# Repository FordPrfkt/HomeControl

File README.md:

# HomeControl
Home automation system build around RFM69

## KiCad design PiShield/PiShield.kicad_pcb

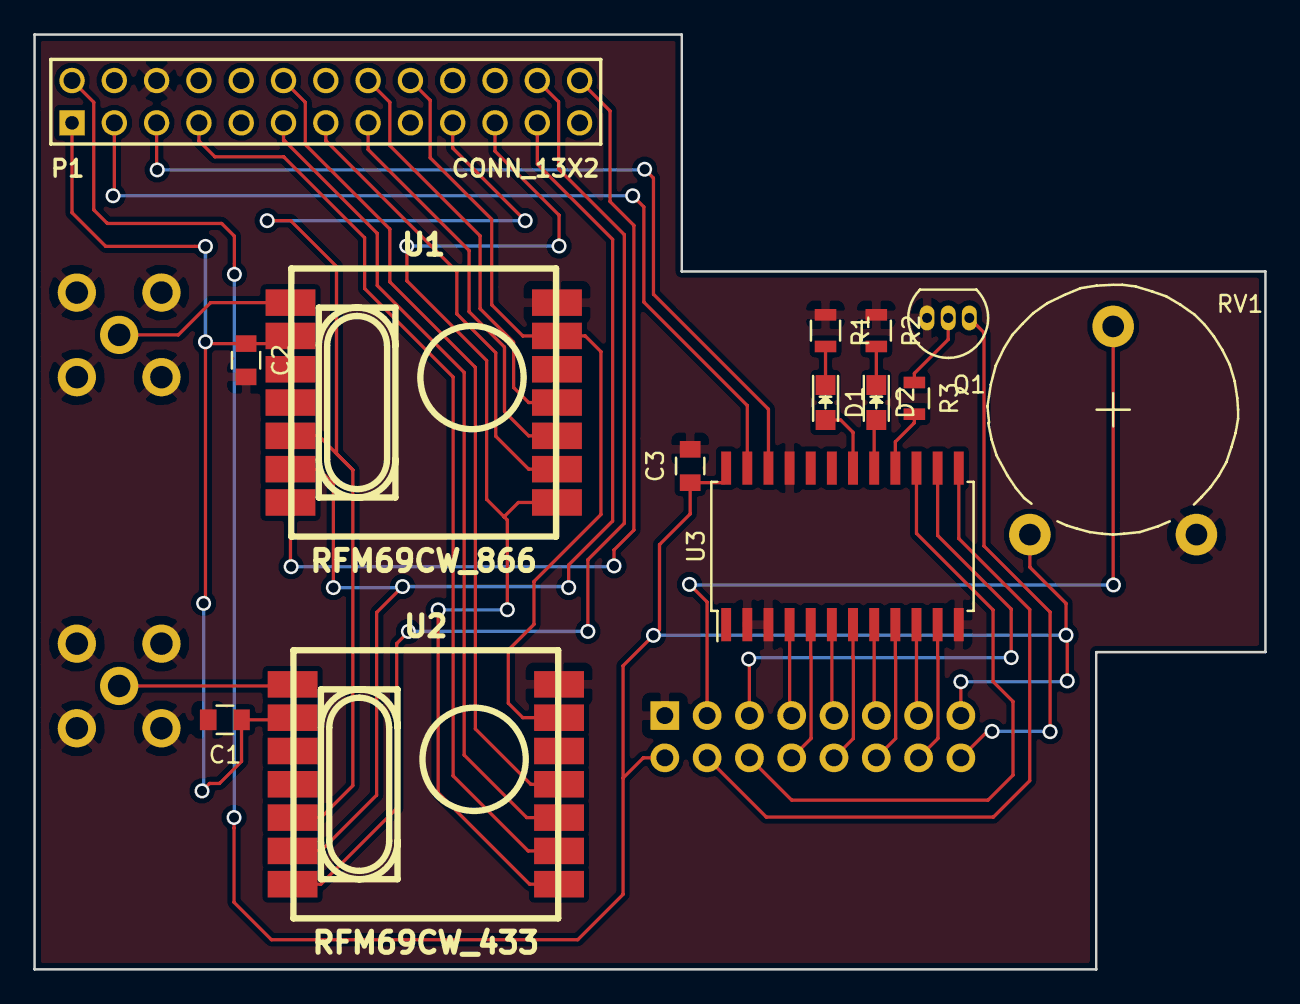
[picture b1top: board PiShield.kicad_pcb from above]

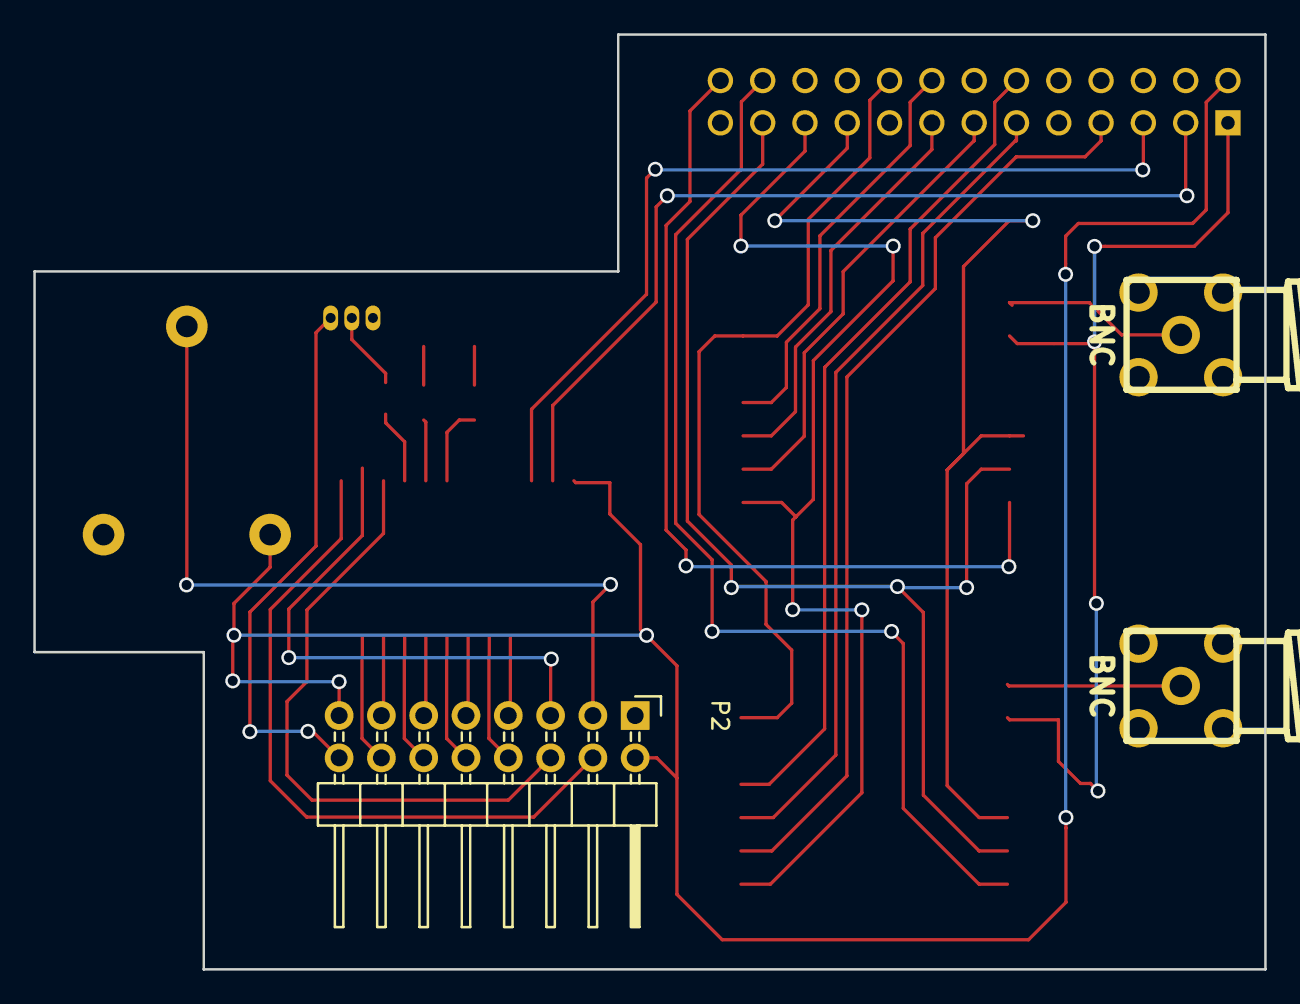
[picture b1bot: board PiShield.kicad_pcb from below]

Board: 2 copper layers, 73.9 x 56.1 mm, 17 parts (3 on the bottom side), 38 nets.

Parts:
C1, C2, C3: 100nF; C_0805
D1, D2: LED; LED_0805
P1: CONN_13X2; pin_array_13x2
P2: CONN_01X16; Pin_Header_Angled_2x08
P3, P4: BNC; sma_90_r300.124.403
Q1: BC547; TO-92_Inline_Narrow_Oval
R1, R2, R3: R; R_0805
RV1: POT; Potentiometer_Trimmer-Piher_PT15-V12-5_horizontal
U1: RFM69CW_866; RFM12B_SMD
U2: RFM69CW_433; RFM12B_SMD
U3: PCA9555; SOIC-24_7.5x15.4mm_Pitch1.27mm

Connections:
+3.3V: C1.1, C2.1, P1.1, U1.2, U2.2
+5V: C3.1, P1.2, P2.2, P2.15, RV1.1, U3.24
CS_433: P1.24, U2.7
CS_866: P1.26, U1.7
DIO0_433: P1.7, U2.9
DIO0_866: P1.13, U1.9
DIO1_433: P1.12, U2.11
DIO1_866: P1.16, U1.11
DIO2_433: P1.11, U2.10
DIO2_866: P1.15, U1.10
GND: C1.2, C2.2, C3.2, P1.6, P2.1, P3.2, P4.2, Q1.3, R1.1, R2.1, RV1.3, U1.14, U2.14, U3.2, U3.3, U3.12, U3.21
MISO: P1.21, U1.8, U2.8
MOSI: P1.19, U1.5, U2.5
unnamed: D1.1, R1.2
unnamed: D1.2, U3.18
unnamed: D2.1, R2.2
unnamed: D2.2, U3.17
unnamed: P2.3, RV1.2
unnamed: P2.4, U3.13
unnamed: P2.5, U3.14
unnamed: P2.6, U3.15
unnamed: P2.7, U3.4
unnamed: P2.8, U3.5
unnamed: P2.9, U3.6
unnamed: P2.10, U3.7
unnamed: P2.11, U3.8
unnamed: P2.12, U3.9
unnamed: P2.13, U3.10
unnamed: P2.14, U3.11
unnamed: P2.16, Q1.1
unnamed: P3.1, U2.1
unnamed: P4.1, U1.1
unnamed: Q1.2, R3.1
unnamed: R3.2, U3.16
Reset_RF: P1.18, U1.13, U2.13
SCK: P1.23, U1.6, U2.6
SCL: P1.5, U3.22
SDA: P1.3, U3.23

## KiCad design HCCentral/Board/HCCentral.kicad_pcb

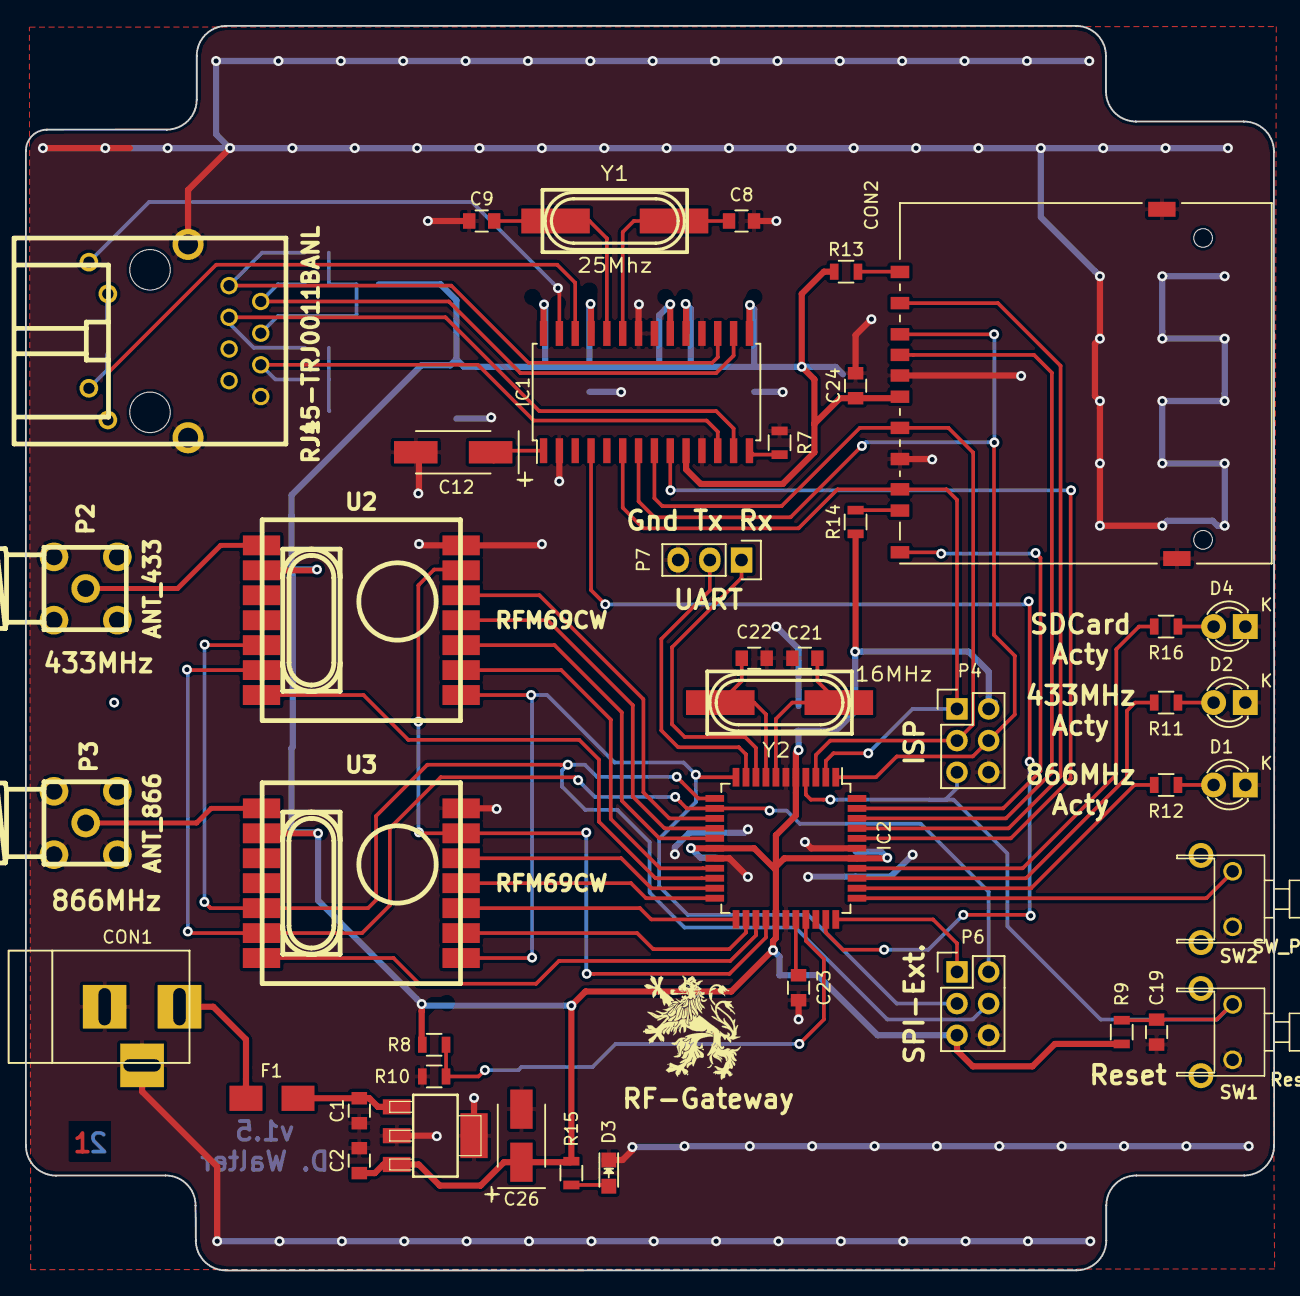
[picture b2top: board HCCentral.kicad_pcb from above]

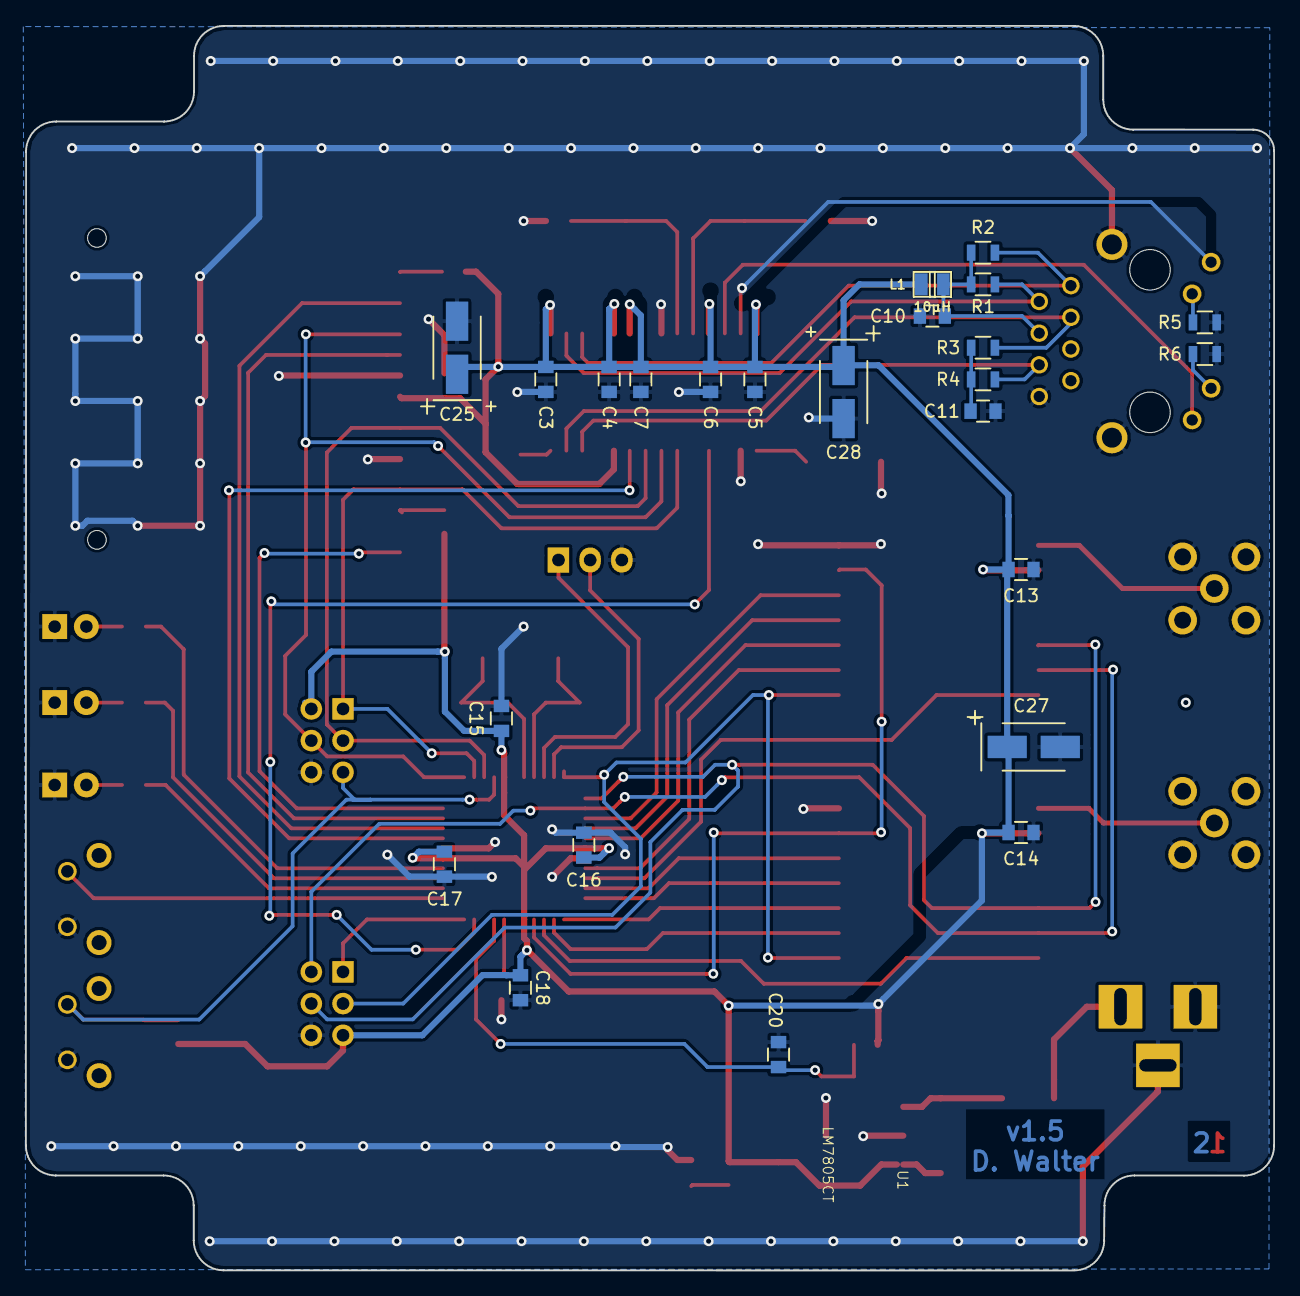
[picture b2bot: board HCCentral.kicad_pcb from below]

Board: 2 copper layers, 100.1 x 99.8 mm, 67 parts (24 on the bottom side), 60 nets.

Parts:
C1: 330nF; C_0805
C2, C3, C4, C5, C6, C7, C10, C11, C13, C14, C15, C16, C17, C18, C19, C20, C23, C24: 100nF; C_0805
C8, C9: 22pF; C_0805
C12: 10µF; TantalC_SizeC_EIA-6032_HandSoldering
C21, C22: 32pF; C_0805
C25, C26, C27, C28: 22µF; TantalC_SizeB_EIA-3528_HandSoldering
CON1: BARREL_JACK
CON2: SD_Card; SD_Card_Receptacle
D1, D2, D4: LED; LED-3MM
D3: LED; LED_0805
F1: 600mAT; Fuse_SMD1206_HandSoldering
IC1: ENC28J60-I/SO; SOIC-28_7.5x17.9mm_Pitch1.27mm
IC2: ATMEGA1284P-A; TQFP-44_10x10mm_Pitch0.8mm
J1: RJ45-TRJ0011BANL; trj0011banl
L1: 10µH; inductor_smd_0805
P2: ANT_433; sma_90_r300.124.403
P3: ANT_866; sma_90_r300.124.403
P4: ISP; Pin_Header_Straight_2x03
P6: SPI; Pin_Header_Straight_2x03
P7: UART; Pin_Header_Straight_1x03
R1, R2, R4: 49,9R; R_0805
R3: 49,9; R_0805
R5, R6, R11, R12, R15, R16: 180R; R_0805
R7: 2k32; R_0805
R8: R; R_0805
R9: 10k; R_0805
R10: 15k; R_0805
R13, R14: 1kR; R_0805
SW1: Reset; SW_0773
SW2: SW_PUSH; SW_0773
U1: LM7805CT; v-reg-78xx-SOT223
U2, U3: RFM69CW; RFM12B_SMD
Y1: 25Mhz; hc-49_smd
Y2: 16MHz; hc-49_smd

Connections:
+3V3: C2.1, C3.2, C4.2, C5.2, C6.2, C7.2, C13.2, C14.2, C15.2, C16.2, C17.2, C18.2, C24.2, C25.1, C26.1, C27.1, C28.1, CON2.4, IC1.10, IC1.15, IC1.19, IC1.20, IC1.25, IC1.28, IC2.5, IC2.17, IC2.27, IC2.38, L1.1, P4.2, P6.5, R8.1, R9.2, R13.2, R14.2, R15.1, U1.3, U2.2, U3.2
/Controller_USB_SD/CS_LAN: IC1.9, IC2.40
/Controller_USB_SD/CS_RF433: IC2.20, U2.7
/Controller_USB_SD/CS_RF866: IC2.25, U3.7
/Controller_USB_SD/DIO0_433: IC2.19, U2.9
/Controller_USB_SD/DIO0_866: IC2.24, U3.9
/Controller_USB_SD/DIO1_433: IC2.15, U2.11
/Controller_USB_SD/DIO1_866: IC2.22, U3.11
/Controller_USB_SD/DIO2_433: IC2.16, U2.10
/Controller_USB_SD/DIO2_866: IC2.23, U3.10
/Controller_USB_SD/DIO5_433: IC2.14, U2.12
/Controller_USB_SD/DIO5_866: IC2.21, U3.12
/Controller_USB_SD/IRQ_LAN: IC1.4, IC2.32
/Controller_USB_SD/MISO_LAN: CON2.7, IC1.6, IC2.2, P4.1
/Controller_USB_SD/MISO_RF: IC2.11, P6.3, U2.8, U3.8
/Controller_USB_SD/MOSI_LAN: CON2.2, IC1.7, IC2.1, P4.4
/Controller_USB_SD/MOSI_RF: IC2.12, P6.4, U2.5, U3.5
/Controller_USB_SD/Reset_RF: IC2.26, U2.13, U3.13
/Controller_USB_SD/SCK_LAN: CON2.5, IC1.8, IC2.3, P4.3
/Controller_USB_SD/SCK_RF: IC2.13, P6.2, U2.6, U3.6
CS_EXT: IC2.33, P6.1
GND: C1.2, C2.2, C3.1, C4.1, C5.1, C6.1, C7.1, C8.2, C9.2, C10.1, C11.1, C12.2, C13.1, C14.1, C15.1, C16.1, C17.1, C18.1, C19.1, C20.1, C21.2, C22.2, C23.1, C24.1, C25.2, C26.2, C27.2, C28.2, CON1.2, CON1.3, CON2.3, CON2.6, CON2.12, CON2.13, D1.1, D2.1, D3.1, D4.1, IC1.2, IC1.11, IC1.18, IC1.21, IC1.22, IC2.6, IC2.18, IC2.28, IC2.39, J1.8, J1.13, P2.2, P3.2, P4.6, P6.6, P7.3, R5.1, R6.1, R7.2, R10.2, SW1.1, SW2.1, U1.2, U2.14, U3.14
unnamed: C1.1, F1.2, U1.1
unnamed: C8.1, IC1.23, Y1.1
unnamed: C9.1, IC1.24, Y1.2
unnamed: C10.2, J1.4, L1.2, R1.2, R2.2
unnamed: C11.2, R3.1, R4.1
unnamed: C12.1, IC1.1
unnamed: C19.2, IC2.4, P4.5, R9.1, SW1.2
unnamed: C20.2, IC2.30, R8.2, R10.1
unnamed: C21.1, IC2.7, Y2.2
unnamed: C22.1, IC2.8, Y2.1
unnamed: C23.2, IC2.29
unnamed: CON1.1, F1.1
unnamed: CON2.1, IC2.41
unnamed: CON2.8, R14.1
unnamed: CON2.9, R13.1
unnamed: CON2.10, IC2.42
unnamed: CON2.11, IC2.43
unnamed: D1.2, R12.1
unnamed: D2.2, R11.1
unnamed: D3.2, R15.2
unnamed: D4.2, R16.1
unnamed: IC1.12, J1.6, R4.2
unnamed: IC1.13, J1.3, R3.2
unnamed: IC1.14, R7.1
unnamed: IC1.16, J1.2, R1.1
unnamed: IC1.17, J1.1, R2.1
unnamed: IC1.26, J1.12
unnamed: IC1.27, J1.9
unnamed: IC2.9, P7.1
unnamed: IC2.10, P7.2
unnamed: IC2.34, SW2.2
unnamed: IC2.35, R12.2
unnamed: IC2.36, R11.2
unnamed: IC2.37, R16.2
unnamed: J1.10, R5.2
unnamed: J1.11, R6.2
unnamed: P2.1, U2.1
unnamed: P3.1, U3.1

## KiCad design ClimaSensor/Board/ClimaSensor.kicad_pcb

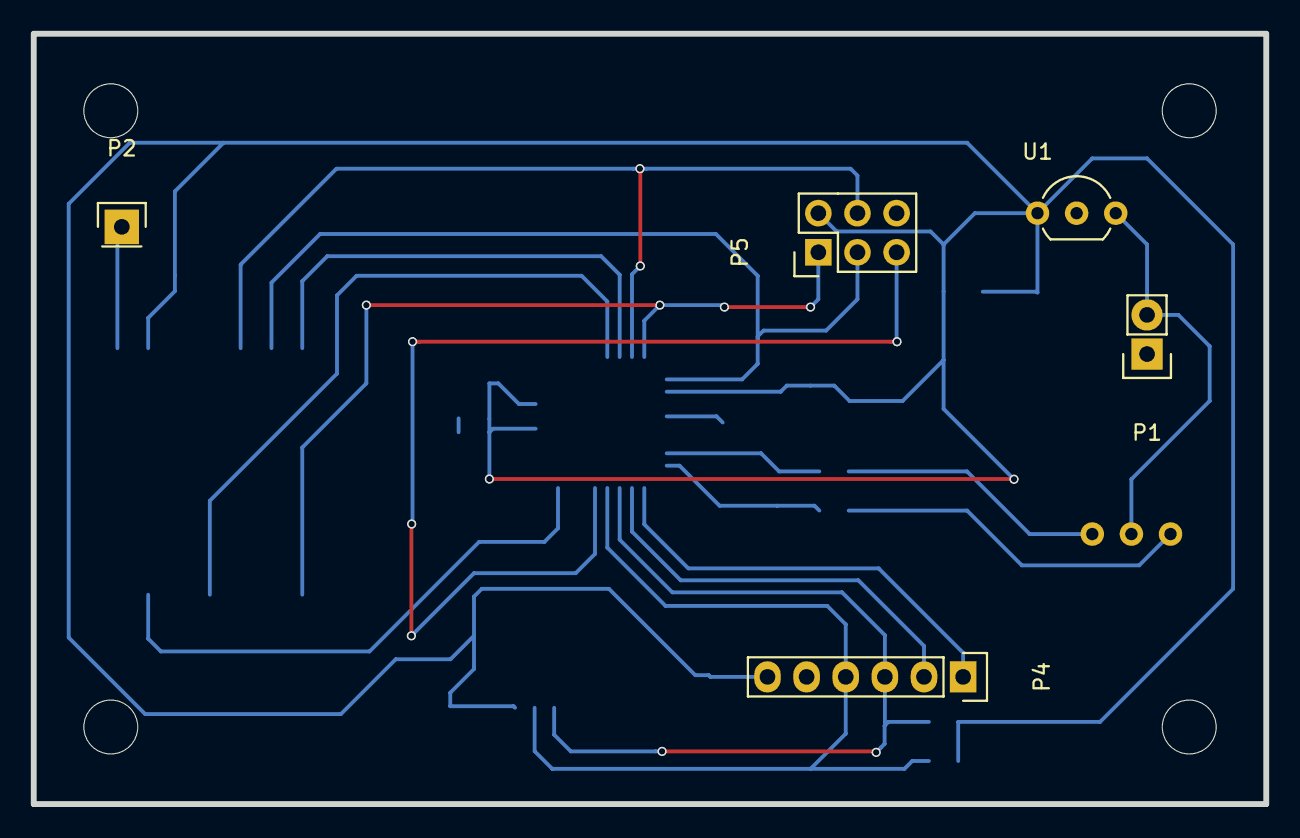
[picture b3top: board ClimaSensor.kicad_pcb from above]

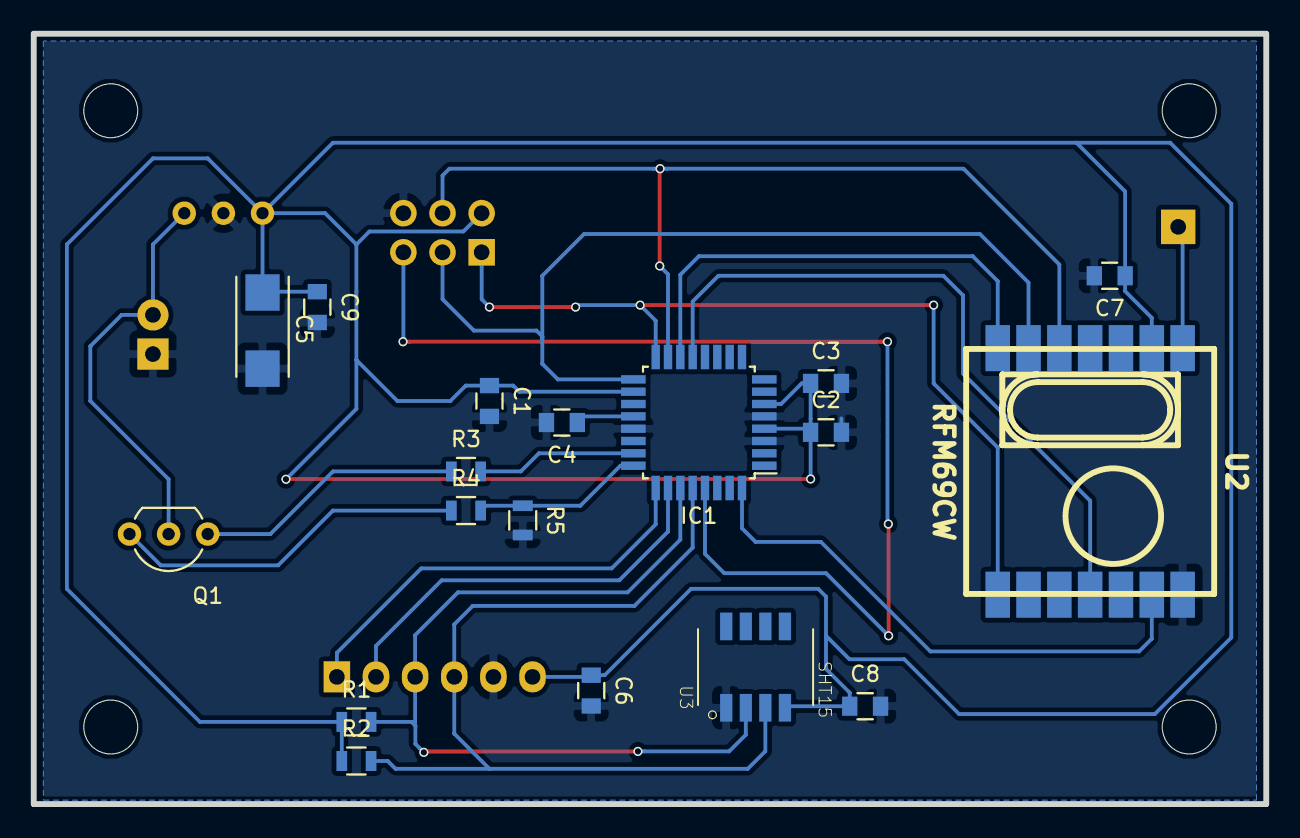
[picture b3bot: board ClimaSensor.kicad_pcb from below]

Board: 2 copper layers, 80.0 x 50.0 mm, 23 parts (18 on the bottom side), 20 nets.

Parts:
C1, C2, C3, C4, C6, C7, C8, C9: 100nF; C_0805
C5: CP; TantalC_SizeC_EIA-6032_Reflow
IC1: ATMEGA88PA-A; TQFP-32_7x7mm_Pitch0.8mm
P1: CONN_01X02; Pin_Header_Straight_1x02
P2: CONN_01X01; Pin_Header_Straight_1x01
P4: MPL115A2; Pin_Header_Straight_1x06
P5: ISP; Pin_Header_Straight_2x03
Q1: Q_NPN_BCE; TO-92_Inline_Wide
R1, R2, R3, R4, R5: R; R_0805
U1: LM2931Z-3.3/5.0; TO-92_Inline_Wide
U2: RFM69CW; RFM12B_SMD
U3: SHT15; DFN747X493X250-8N

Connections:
+3V3: C1.1, C2.1, C3.1, C5.1, C6.1, C7.1, C8.1, C9.1, IC1.4, IC1.6, IC1.18, P4.6, P5.2, R1.1, R2.1, U1.1, U2.2, U3.4
+BATT: P1.2, Q1.2, U1.3
GND: C1.2, C2.2, C3.2, C4.2, C5.2, C6.2, C7.2, C8.2, C9.2, IC1.3, IC1.5, IC1.21, P1.1, P4.5, P5.6, R5.2, U1.2, U2.14, U3.1
unnamed: C4.1, IC1.20
unnamed: IC1.13, U2.11
unnamed: IC1.14, U2.7
unnamed: IC1.15, P5.4, U2.5
unnamed: IC1.16, P5.1, U2.8
unnamed: IC1.17, P5.3, U2.6
unnamed: IC1.23, R3.2
unnamed: IC1.24, R4.2, R5.1
unnamed: IC1.25, P4.1
unnamed: IC1.26, P4.2
unnamed: IC1.27, P4.3, R1.2, U3.2
unnamed: IC1.28, P4.4, R2.2, U3.3
unnamed: IC1.29, P5.5
unnamed: IC1.32, U2.13
unnamed: P2.1, U2.1
unnamed: Q1.1, R3.1
unnamed: Q1.3, R4.1

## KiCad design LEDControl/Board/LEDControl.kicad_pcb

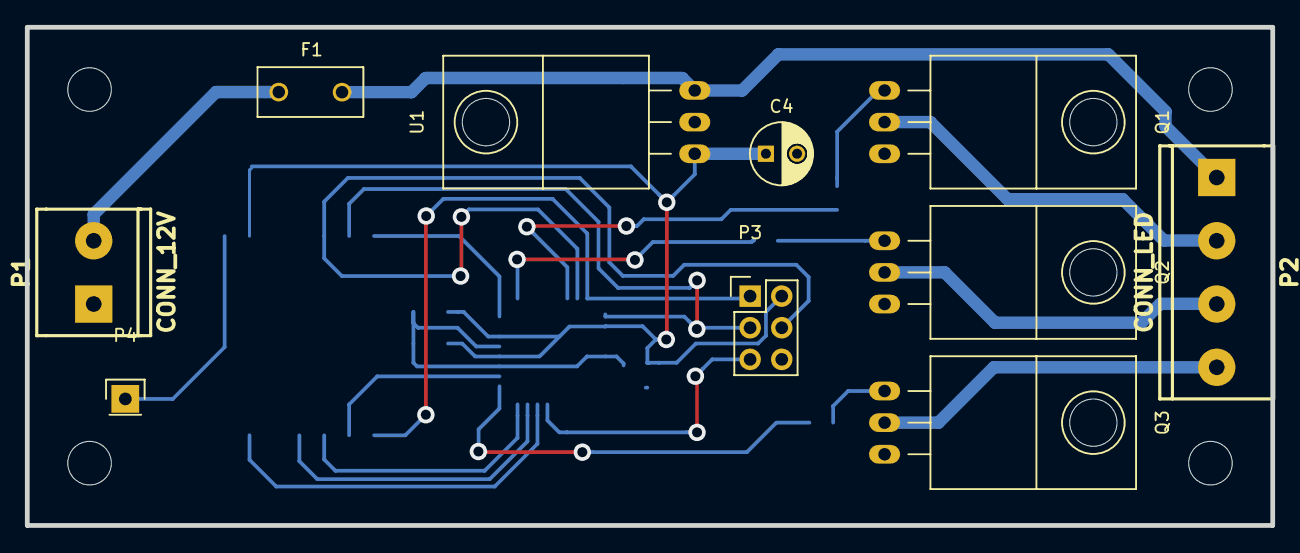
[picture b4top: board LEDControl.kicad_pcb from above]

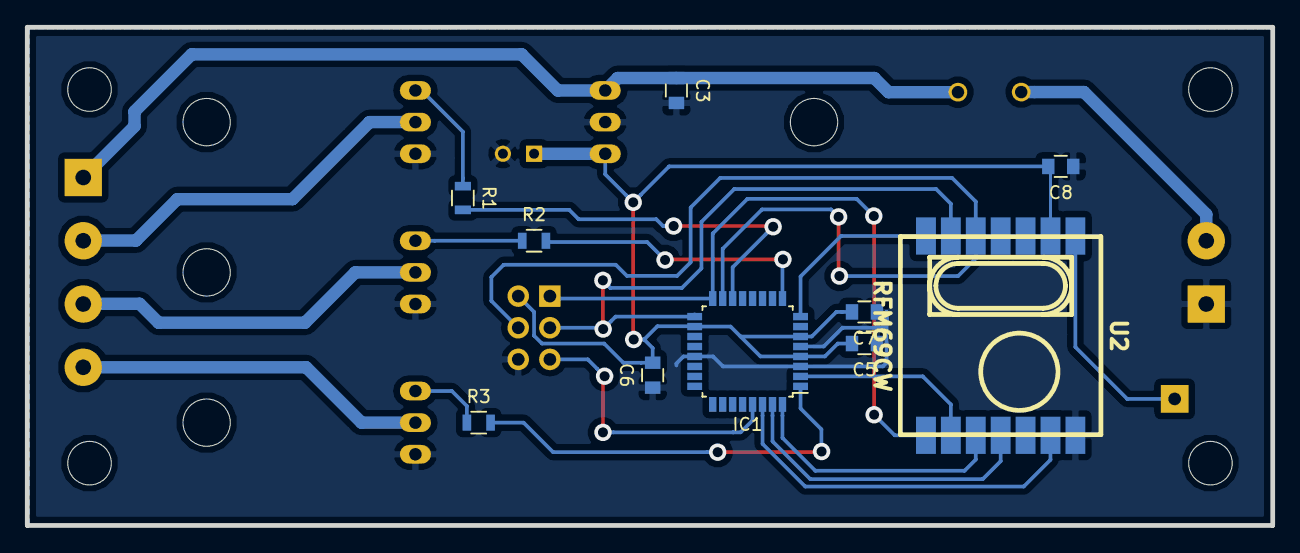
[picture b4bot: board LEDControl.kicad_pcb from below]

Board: 2 copper layers, 100.0 x 40.0 mm, 20 parts (10 on the bottom side), 23 nets.

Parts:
C3, C5, C6, C7, C8: 100nF; C_0805
C4: 10µF; C_Radial_D5_L6_P2.5
F1: 2AT; Fuse_TE5_Littlefuse-395Series
IC1: ATMEGA88PA-M; LQFP-32_7x7mm_Pitch0.8mm
P1: CONN_12V; mors_2p
P2: CONN_LED; mors_4p
P3: CONN_ISP; Pin_Header_Straight_2x03
P4: CONN_01X01; Pin_Header_Straight_1x01
Q1, Q2, Q3: IRLZ34N; TO-220_Neutral123_Horizontal
R1, R2, R3: 100R; R_0805
U1: LM2931AZ-3.3/5.0; TO-220_Neutral123_Horizontal
U2: RFM69CW; RFM12B_SMD

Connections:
+3V3: C4.1, C5.2, C6.2, C7.2, C8.2, IC1.4, IC1.6, IC1.18, P3.2, U1.1, U2.2
+12V: C3.1, F1.2, P2.1, U1.3
GND: C3.2, C4.2, C5.1, C6.1, C7.1, C8.1, IC1.3, IC1.5, IC1.21, P1.1, P3.6, Q1.3, Q2.3, Q3.3, U1.2, U2.14
unnamed: F1.1, P1.2
unnamed: IC1.1, R3.2
unnamed: IC1.2, U2.9
unnamed: IC1.8, U2.7
unnamed: IC1.9, R2.2
unnamed: IC1.14, R1.2
unnamed: IC1.15, P3.4, U2.5
unnamed: IC1.16, P3.1, U2.8
unnamed: IC1.17, P3.3, U2.6
unnamed: IC1.29, P3.5
unnamed: IC1.30, U2.13
unnamed: IC1.31, U2.11
unnamed: IC1.32, U2.10
unnamed: P2.2, Q1.2
unnamed: P2.3, Q2.2
unnamed: P2.4, Q3.2
unnamed: P4.1, U2.1
unnamed: Q1.1, R1.1
unnamed: Q2.1, R2.1
unnamed: Q3.1, R3.1

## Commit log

2016-03-01 Dateien in richtiges Verzeichnis verschoben
2016-03-15 Layouting...
2016-03-27 PiShield neu angelegt
2016-04-27 Layout aktualisiert, 10x10cm
2016-04-28 Layout zur Fertigung
2016-05-03 Removed PiShield
2016-05-03 Production files, Updated 3D Models
2016-05-03 Created ClimaSensor Board
2016-05-03 Created Power Sensor Board
2016-05-19 Deleted Gerbers, Updated V1.5
2016-05-19 Added My ethersex fork under Software
2016-05-19 Fixed Line Endings
2016-05-19 Fixed script for cygwin
2016-05-19 Added configuration for board
2016-05-21 Begin chaning SPI to support multiple interfaces
2016-05-27 SPI does now support multiple interfaces
2016-05-29 Fixed XCK Pin not as output Fixed error in config.in Added SPI channel to SD Card and RFM12 code
2016-07-04 Work in Progress
2016-07-11 Work in Progress..
2017-02-01 Added MINGW
2017-02-01 Fixed sed for MSYS
